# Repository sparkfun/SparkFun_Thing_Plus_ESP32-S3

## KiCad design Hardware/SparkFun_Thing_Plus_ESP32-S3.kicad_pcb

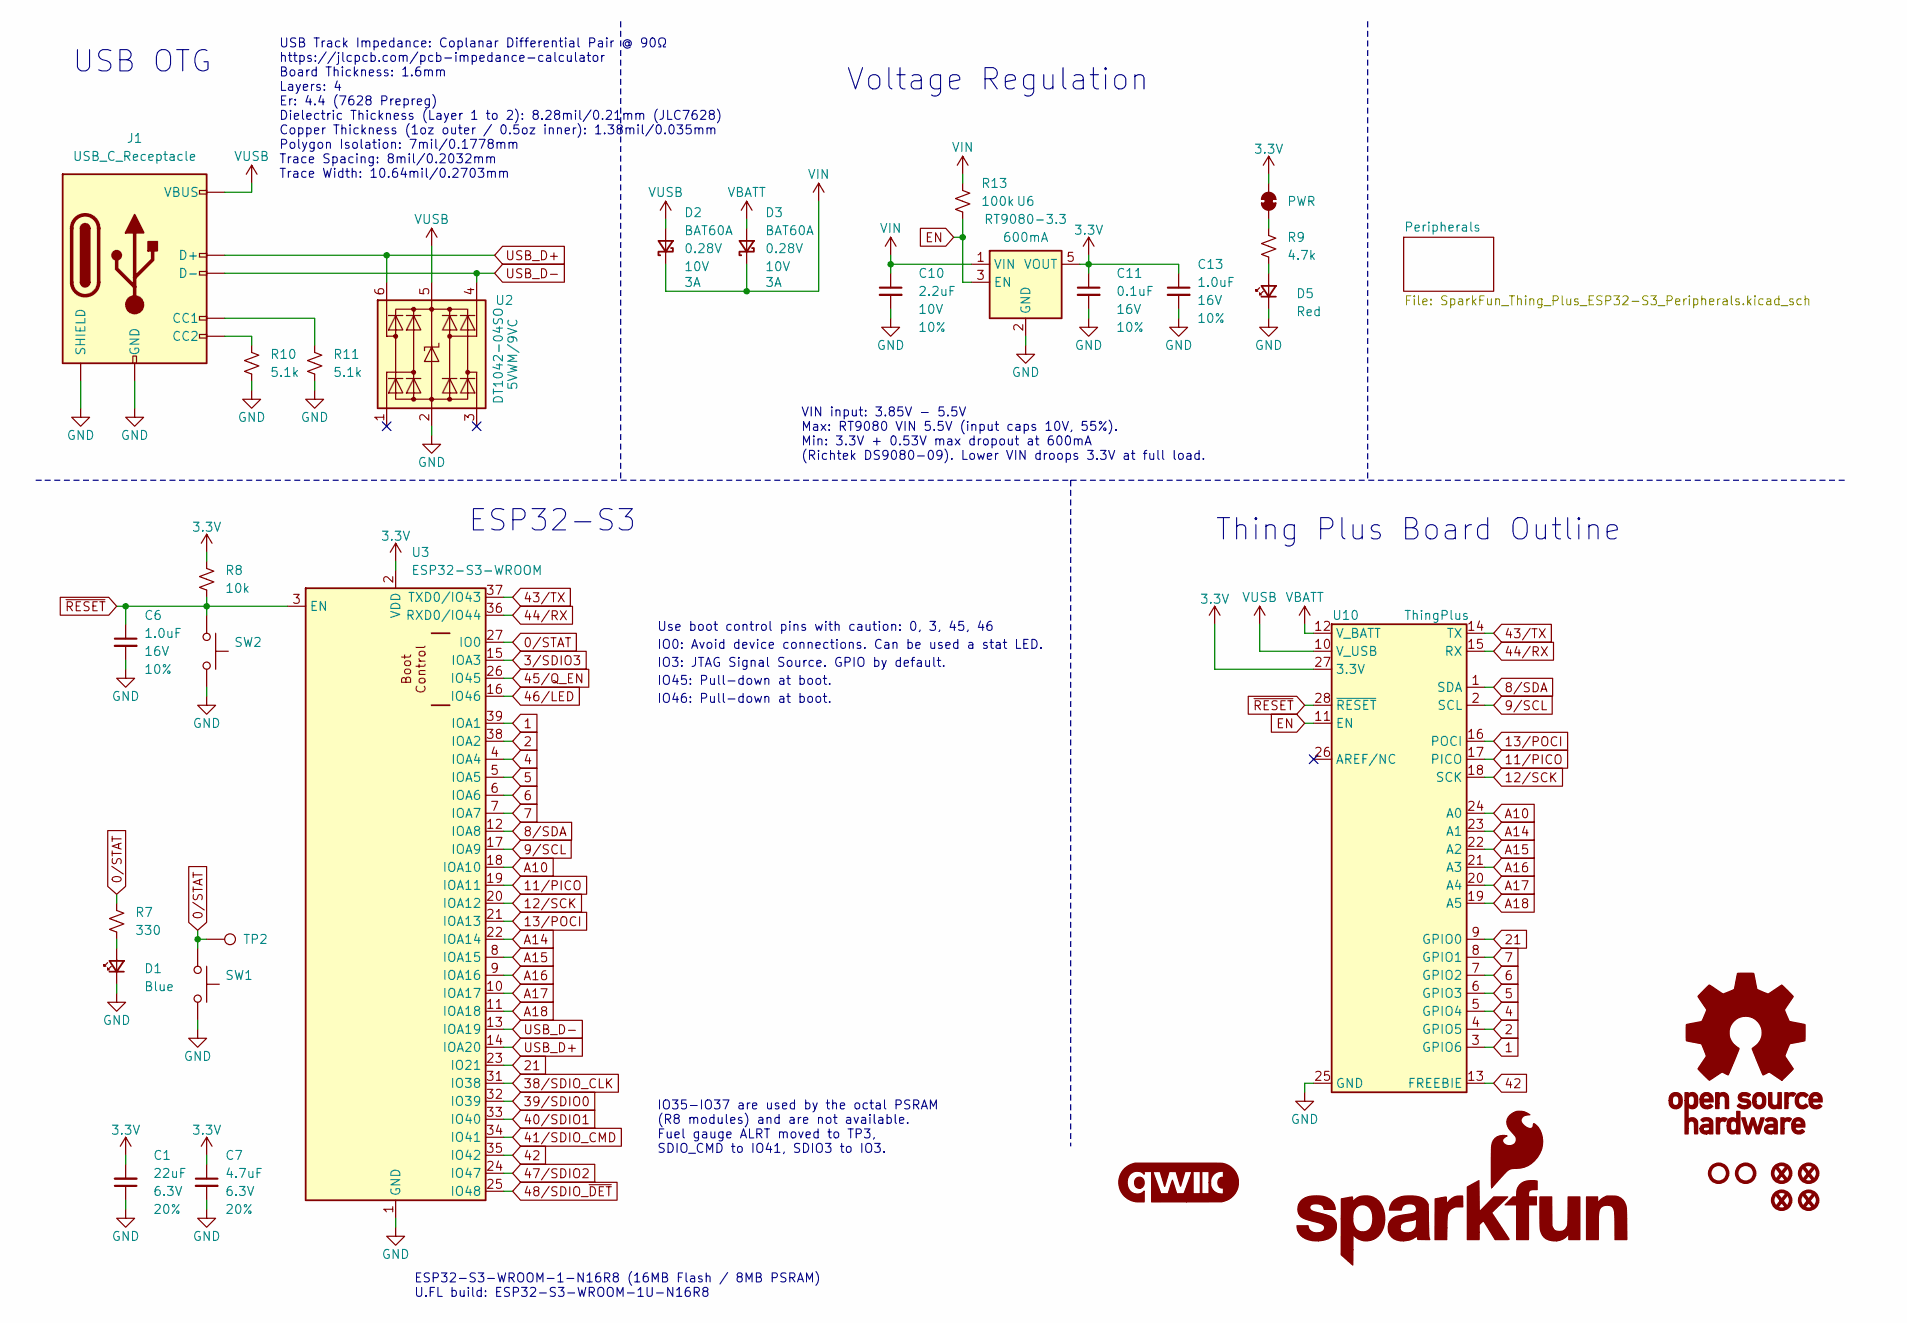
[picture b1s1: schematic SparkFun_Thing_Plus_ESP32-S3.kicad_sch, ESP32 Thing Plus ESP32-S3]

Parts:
C1: 22uF; C_0603_1608Metric; Voltage 6.3V; Tolerance 20%
C6, C13: 1.0uF; C_0402_1005Metric; Voltage 16V; Tolerance 10%
C7: 4.7uF; C_0402_1005Metric; Voltage 6.3V; Tolerance 20%
C10: 2.2uF; C_0402_1005Metric; Voltage 10V; Tolerance 10%
C11: 0.1uF; C_0402_1005Metric; Voltage 16V; Tolerance 10%
D1: Blue; LED_0603_1608Metric_Blue
D2, D3: BAT60A; SOD-323
D5: Red; LED_0603_1608Metric_Red
FID1, FID2, FID3, FID4: Fiducial_0.5mm; Fiducial_0.5mm_Mask1mm
G1: qwiic_Logo
G2: SparkFun_Logo
G3: OSHW_Logo; Creative_Commons_License
J1: USB_C_Receptacle; USB-C_16
JP1: PWR; Jumper_2_NC_Trace
R7: 330; R_0402_1005Metric
R8: 10k; R_0402_1005Metric
R9: 4.7k; R_0402_1005Metric
R10, R11: 5.1k; R_0402_1005Metric
R13: 100k; R_0402_1005Metric
ST1, ST3: Standoff
SW1, SW2: SMD_4.6x2.8mm_h2.5mm; Push_SMD_4.6x2.8mm_h2.5mm
TP2: 1.0mm; TestPoint-1.0mm
U2: DT1042-04SO; SOT23-6; Rating 5VWM/9VC
U3: ESP32-S3-WROOM; ESP32-S3-WROOM-1
U6: RT9080-3.3; SOT23-5
U10: ThingPlus

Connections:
0/STAT: R7.2, SW1.1, TP2.1 (1_1), U3.27 (IO0)
1: U3.39 (IOA1), U10.3 (GPIO6)
2: U3.38 (IOA2), U10.4 (GPIO5)
3.3V: C1.2, C7.1, C11.1, C13.1, JP1.2 (B), R8.2, U3.2 (VDD), U6.5 (VOUT), U10.27 (3.3V); also elsewhere on the board
3/SDIO3: U3.15 (IOA3); also elsewhere on the board
4: U3.4 (IOA4), U10.5 (GPIO4)
5: U3.5 (IOA5), U10.6 (GPIO3)
6: U3.6 (IOA6), U10.7 (GPIO2)
7: U3.7 (IOA7), U10.8 (GPIO1)
8/SDA: U3.12 (IOA8), U10.1 (SDA); also elsewhere on the board
9/SCL: U3.17 (IOA9), U10.2 (SCL); also elsewhere on the board
11/PICO: U3.19 (IOA11), U10.17 (PICO)
12/SCK: U3.20 (IOA12), U10.18 (SCK)
13/POCI: U3.21 (IOA13), U10.16 (POCI)
21: U3.23 (IO21), U10.9 (GPIO0)
38/SDIO_CLK: U3.31 (IO38); also elsewhere on the board
39/SDIO0: U3.32 (IO39); also elsewhere on the board
40/SDIO1: U3.33 (IO40); also elsewhere on the board
41/SDIO_CMD: U3.34 (IO41); also elsewhere on the board
42: U3.35 (IO42), U10.13 (FREEBIE)
43/TX: U3.37 (TXD0/IO43), U10.14 (TX)
44/RX: U3.36 (RXD0/IO44), U10.15 (RX)
45/Q_EN: U3.26 (IO45); also elsewhere on the board
46/LED: U3.16 (IO46); also elsewhere on the board
47/SDIO2: U3.24 (IO47); also elsewhere on the board
48/SDIO_~DET: U3.25 (IO48); also elsewhere on the board
A10: U3.18 (IOA10), U10.24 (A0)
A14: U3.22 (IOA14), U10.23 (A1)
A15: U3.8 (IOA15), U10.22 (A2)
A16: U3.9 (IOA16), U10.21 (A3)
A17: U3.10 (IOA17), U10.20 (A4)
A18: U3.11 (IOA18), U10.19 (A5)
EN: R13.1, U6.3 (EN), U10.11 (EN)
GND: C1.1, C6.2, C7.2, C10.2, C11.2, C13.2, D1.1 (K), D5.1 (K), J1.GND, J1.S (SHIELD), R10.2, R11.1, SW1.2, SW2.2, U2.2 (GND), U3.1 (GND), U3.40 (GND), U3.41.1 (GND), U3.41.2 (GND), U3.41.3 (GND), U3.41.4 (GND), U3.41.5 (GND), U3.41.6 (GND), U3.41.7 (GND), U3.41.8 (GND), U3.41.9 (GND), U6.2 (GND), U10.25 (GND); also elsewhere on the board
unnamed: D1.2 (A), R7.1
unnamed: D5.2 (A), R9.1
unnamed: J1.A5 (CC1), R11.2
unnamed: J1.B5 (CC2), R10.1
unnamed: JP1.1 (A), R9.2
USB_D+: J1.A6 (D+), J1.B6 (D+), U2.6 (I/O4), U3.14 (IOA20)
USB_D-: J1.A7 (D-), J1.B7 (D-), U2.4 (I/O3), U3.13 (IOA19)
VBATT: D3.2 (A), U10.12 (V_BATT); also elsewhere on the board
VIN: C10.1, D2.1 (K), D3.1 (K), R13.2, U6.1 (VIN); also elsewhere on the board
VUSB: D2.2 (A), J1.VBUS, U2.5 (VCC), U10.10 (V_USB); also elsewhere on the board
~RESET: C6.1, R8.1, SW2.1, U3.3 (EN), U10.28 (~RESET)

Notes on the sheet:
Thing Plus Board Outline
ESP32-S3
IO46: Pull-down at boot.
IO35-IO37 are used by the octal PSRAM (R8 modules) and are not available. Fuel gauge ALRT moved to TP3, SDIO_CMD to IO41, SDIO3 to IO3.
IO45: Pull-down at boot.
IO3: JTAG Signal Source. GPIO by default.
USB OTG
ESP32-S3-WROOM-1-N16R8 (16MB Flash / 8MB PSRAM) U.FL build: ESP32-S3-WROOM-1U-N16R8
Voltage Regulation
IO0: Avoid device connections. Can be used a stat LED.
VIN input: 3.85V - 5.5V Max: RT9080 VIN 5.5V (input caps 10V, 55%). Min: 3.3V + 0.53V max dropout at 600mA (Richtek DS9080-09). Lower VIN droops 3.3V at full load.
Use boot control pins with caution: 0, 3, 45, 46
USB Track Impedance: Coplanar Differential Pair @ 90Ω https://jlcpcb.com/pcb-impedance-calculator Board Thickness: 1.6mm Layers: 4 Er: 4.4 (7628 Prepreg) Dielectric Thickness (Layer 1 to 2): 8.28mil/0.21mm (JLC7628) Copper Thickness (1oz outer / 0.5oz inner): 1.38mil/0.035mm Polygon Isolation: 7mil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

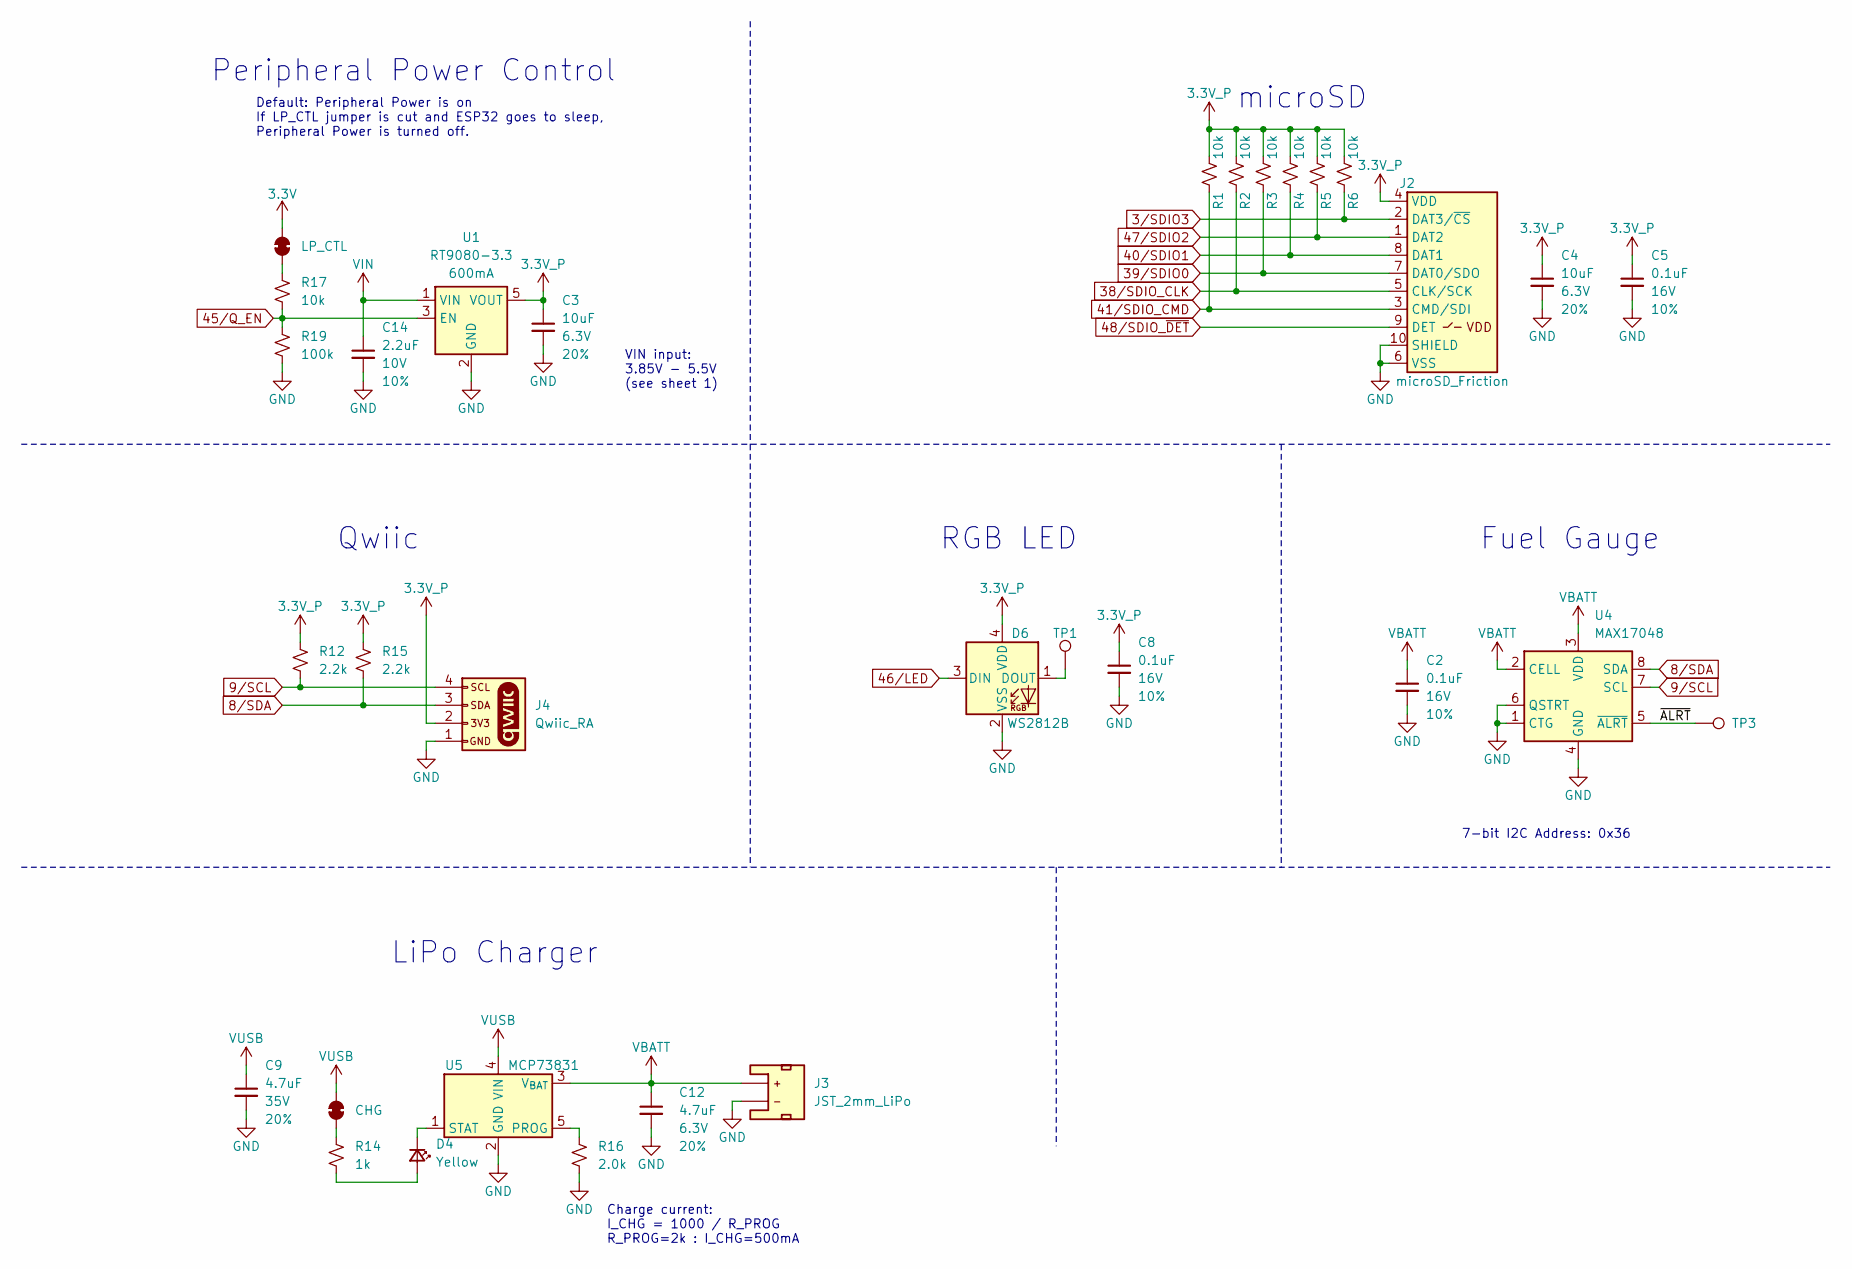
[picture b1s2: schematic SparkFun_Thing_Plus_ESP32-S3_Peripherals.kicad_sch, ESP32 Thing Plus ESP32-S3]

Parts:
C2, C5, C8: 0.1uF; C_0402_1005Metric; Voltage 16V; Tolerance 10%
C3, C4: 10uF; C_0402_1005Metric; Voltage 6.3V; Tolerance 20%
C9: 4.7uF; C_0603_1608Metric; Voltage 35V; Tolerance 20%
C12: 4.7uF; C_0402_1005Metric; Voltage 6.3V; Tolerance 20%
C14: 2.2uF; C_0402_1005Metric; Voltage 10V; Tolerance 10%
D4: Yellow; LED_0603_1608Metric_Yellow
D6: WS2812B; WS2812_2020
J2: microSD_Friction; microSD_Friction_Fit_Common
J3: JST_2mm_LiPo; JST_1x02_P2.0mm_Horizontal_SMD
J4: Qwiic_RA; JST_1x04_P1.0mm_Horizontal_SMD
JP2: LP_CTL; Jumper_2_NC_Trace
JP3: CHG; Jumper_2_NC_Trace
R1, R2, R3, R4, R5, R6, R17: 10k; R_0402_1005Metric
R12, R15: 2.2k; R_0402_1005Metric
R14: 1k; R_0402_1005Metric
R16: 2.0k; R_0402_1005Metric
R19: 100k; R_0402_1005Metric
TP1, TP3: 1.0mm; TestPoint-1.0mm
U1: RT9080-3.3; SOT23-5
U4: MAX17048; DFN-8_2x2mm_P0.5mm_EP1.2x0.8mm
U5: MCP73831; SOT23-5

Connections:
3.3V: JP2.2 (B); also elsewhere on the board
3.3V_P: C3.1, C4.1, C5.1, C8.1, D6.4 (VDD), J2.4 (VDD), J4.2, R1.2, R2.2, R3.2, R4.2, R5.2, R6.2, R12.2, R15.2, U1.5 (VOUT)
3/SDIO3: J2.2 (DAT3/~CS), R6.1; also elsewhere on the board
8/SDA: J4.3, R15.1, U4.8 (SDA); also elsewhere on the board
9/SCL: J4.4, R12.1, U4.7 (SCL); also elsewhere on the board
38/SDIO_CLK: J2.5 (CLK/SCK), R2.1; also elsewhere on the board
39/SDIO0: J2.7 (DAT0/SDO), R3.1; also elsewhere on the board
40/SDIO1: J2.8 (DAT1), R4.1; also elsewhere on the board
41/SDIO_CMD: J2.3 (CMD/SDI), R1.1; also elsewhere on the board
45/Q_EN: R17.1, R19.2, U1.3 (EN); also elsewhere on the board
46/LED: D6.3 (DIN); also elsewhere on the board
47/SDIO2: J2.1 (DAT2), R5.1; also elsewhere on the board
48/SDIO_~DET: J2.9 (DET); also elsewhere on the board
/Peripherals/~ALRT: TP3.1 (1_1), U4.5 (~ALRT)
GND: C2.2, C3.2, C4.2, C5.2, C8.2, C9.2, C12.2, C14.2, D6.2 (VSS), J2.6 (VSS), J2.10 (SHIELD), J3.1 (-), J4.1, R16.1, R19.1, U1.2 (GND), U4.1 (CTG), U4.4 (GND), U4.6 (QSTRT), U4.9 (GND), U5.2 (GND); also elsewhere on the board
unnamed: D4.2 (A), R14.2
unnamed: D4.1 (K), U5.1 (STAT)
unnamed: D6.1 (DOUT), TP1.1 (1_1)
unnamed: JP2.1 (A), R17.2
unnamed: JP3.1 (A), R14.1
unnamed: R16.2, U5.5 (PROG)
VBATT: C2.1, C12.1, J3.2 (+), U4.2 (CELL), U4.3 (VDD), U5.3 (V_{BAT}); also elsewhere on the board
VIN: C14.1, U1.1 (VIN); also elsewhere on the board
VUSB: C9.1, JP3.2 (B), U5.4 (VIN); also elsewhere on the board

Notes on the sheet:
LiPo Charger
Default: Peripheral Power is on If LP_CTL jumper is cut and ESP32 goes to sleep, Peripheral Power is turned off.
Qwiic
Fuel Gauge
microSD
Charge current: I_CHG = 1000 / R_PROG R_PROG=2k : I_CHG=500mA
RGB LED
Peripheral Power Control
VIN input: 3.85V - 5.5V (see sheet 1)
7-bit I2C Address: 0x36

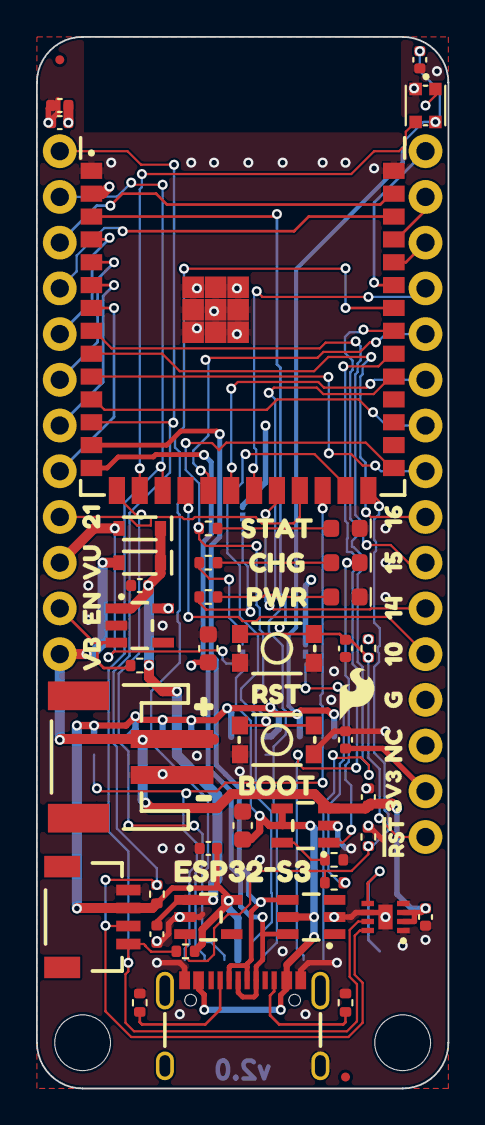
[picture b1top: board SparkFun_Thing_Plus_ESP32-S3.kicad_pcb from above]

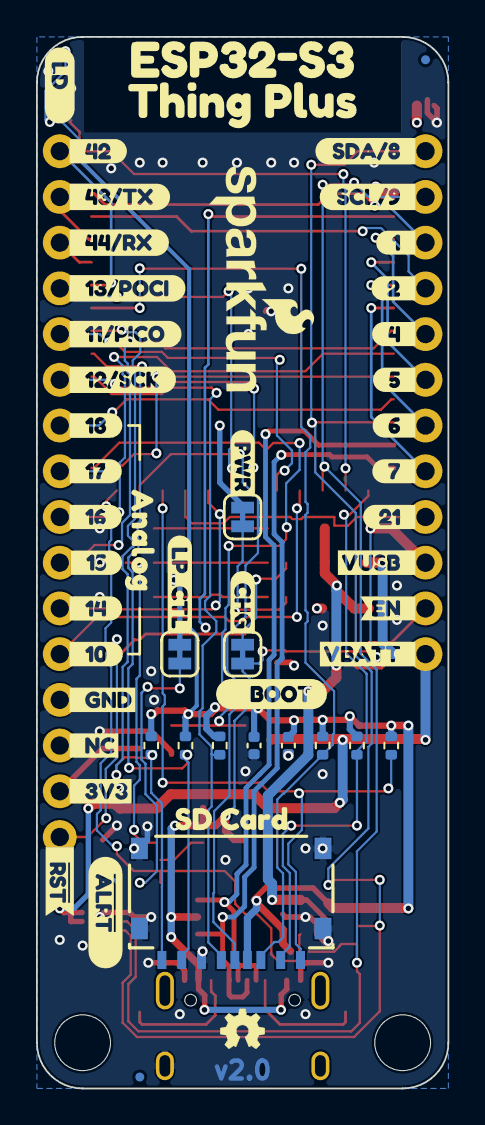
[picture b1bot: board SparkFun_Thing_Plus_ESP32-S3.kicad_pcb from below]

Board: 4 copper layers, 22.9 x 58.4 mm, 124 parts (56 on the bottom side), 53 nets.

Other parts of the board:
Ref**: Val**; OSHW_Logo_2.5mm
kibuzzard-6ADFB170, kibuzzard-6ADFB171, kibuzzard-6ADFC503, kibuzzard-65A992E3, kibuzzard-65A9923A, kibuzzard-65A9926C, kibuzzard-65A9926F, kibuzzard-65A9927C, kibuzzard-65A9927F, kibuzzard-65A9928A, kibuzzard-65A9928E, kibuzzard-65A9933C, kibuzzard-65A9934B, kibuzzard-65A9935C, kibuzzard-65A9936B, kibuzzard-65A99252, kibuzzard-65A99268, kibuzzard-65A99274, kibuzzard-65A99278, kibuzzard-65A99287, kibuzzard-65A99292, kibuzzard-65A99297, kibuzzard-65A99335, kibuzzard-65A99346, kibuzzard-65A99350, kibuzzard-65A99354, kibuzzard-65A99359, kibuzzard-65A99360, kibuzzard-65A99364, kibuzzard-65A99367, kibuzzard-65AA9C9F, kibuzzard-656A32FE: G***; Generated with KiBuzzard
kibuzzard-6ADFBFCF: G***; kibuzzard-6ADFBFCF
kibuzzard-6AE2BC85: G***; kibuzzard-6AE2BC85
kibuzzard-6AE2BC96: G***; kibuzzard-6AE2BC96
kibuzzard-6AFE2CAE: G***; kibuzzard-6AFE2CAE
kibuzzard-65A99A9C: G***; kibuzzard-65A99A9C
kibuzzard-65A99AA3: G***; kibuzzard-65A99AA3
kibuzzard-65A99E72: G***; kibuzzard-65A99E72
kibuzzard-65A403E0: G***; kibuzzard-65A403E0
kibuzzard-65A9990D: G***; kibuzzard-65A9990D
kibuzzard-65A99912: G***; kibuzzard-65A99912
kibuzzard-656A3D93: G***; kibuzzard-656A3D93
kibuzzard-656A31AF: G***; kibuzzard-656A31AF
kibuzzard-656A35A5: G***; kibuzzard-656A35A5
kibuzzard-656A35B5: G***; kibuzzard-656A35B5
kibuzzard-656A35BC: G***; kibuzzard-656A35BC
kibuzzard-656A35C4: G***; kibuzzard-656A35C4
kibuzzard-656A359E: G***; kibuzzard-656A359E
kibuzzard-656A361F: G***; kibuzzard-656A361F
kibuzzard-656A482A: G***; kibuzzard-656A482A
kibuzzard-656A4896: G***; kibuzzard-656A4896
kibuzzard-6569BE4A: G***; kibuzzard-6569BE4A
kibuzzard-6569BE28: G***; kibuzzard-6569BE28
kibuzzard-6569BE57: G***; kibuzzard-6569BE57
kibuzzard-6569BF02: G***; kibuzzard-6569BF02
kibuzzard-6569F7FC: G***; kibuzzard-6569F7FC
kibuzzard-6569F8A4: G***; kibuzzard-6569F8A4

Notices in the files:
parts and their libraries:
Released under the Creative Commons Attribution Share-Alike 4.0 License
https://creativecommons.org/licenses/by-sa/4.0
